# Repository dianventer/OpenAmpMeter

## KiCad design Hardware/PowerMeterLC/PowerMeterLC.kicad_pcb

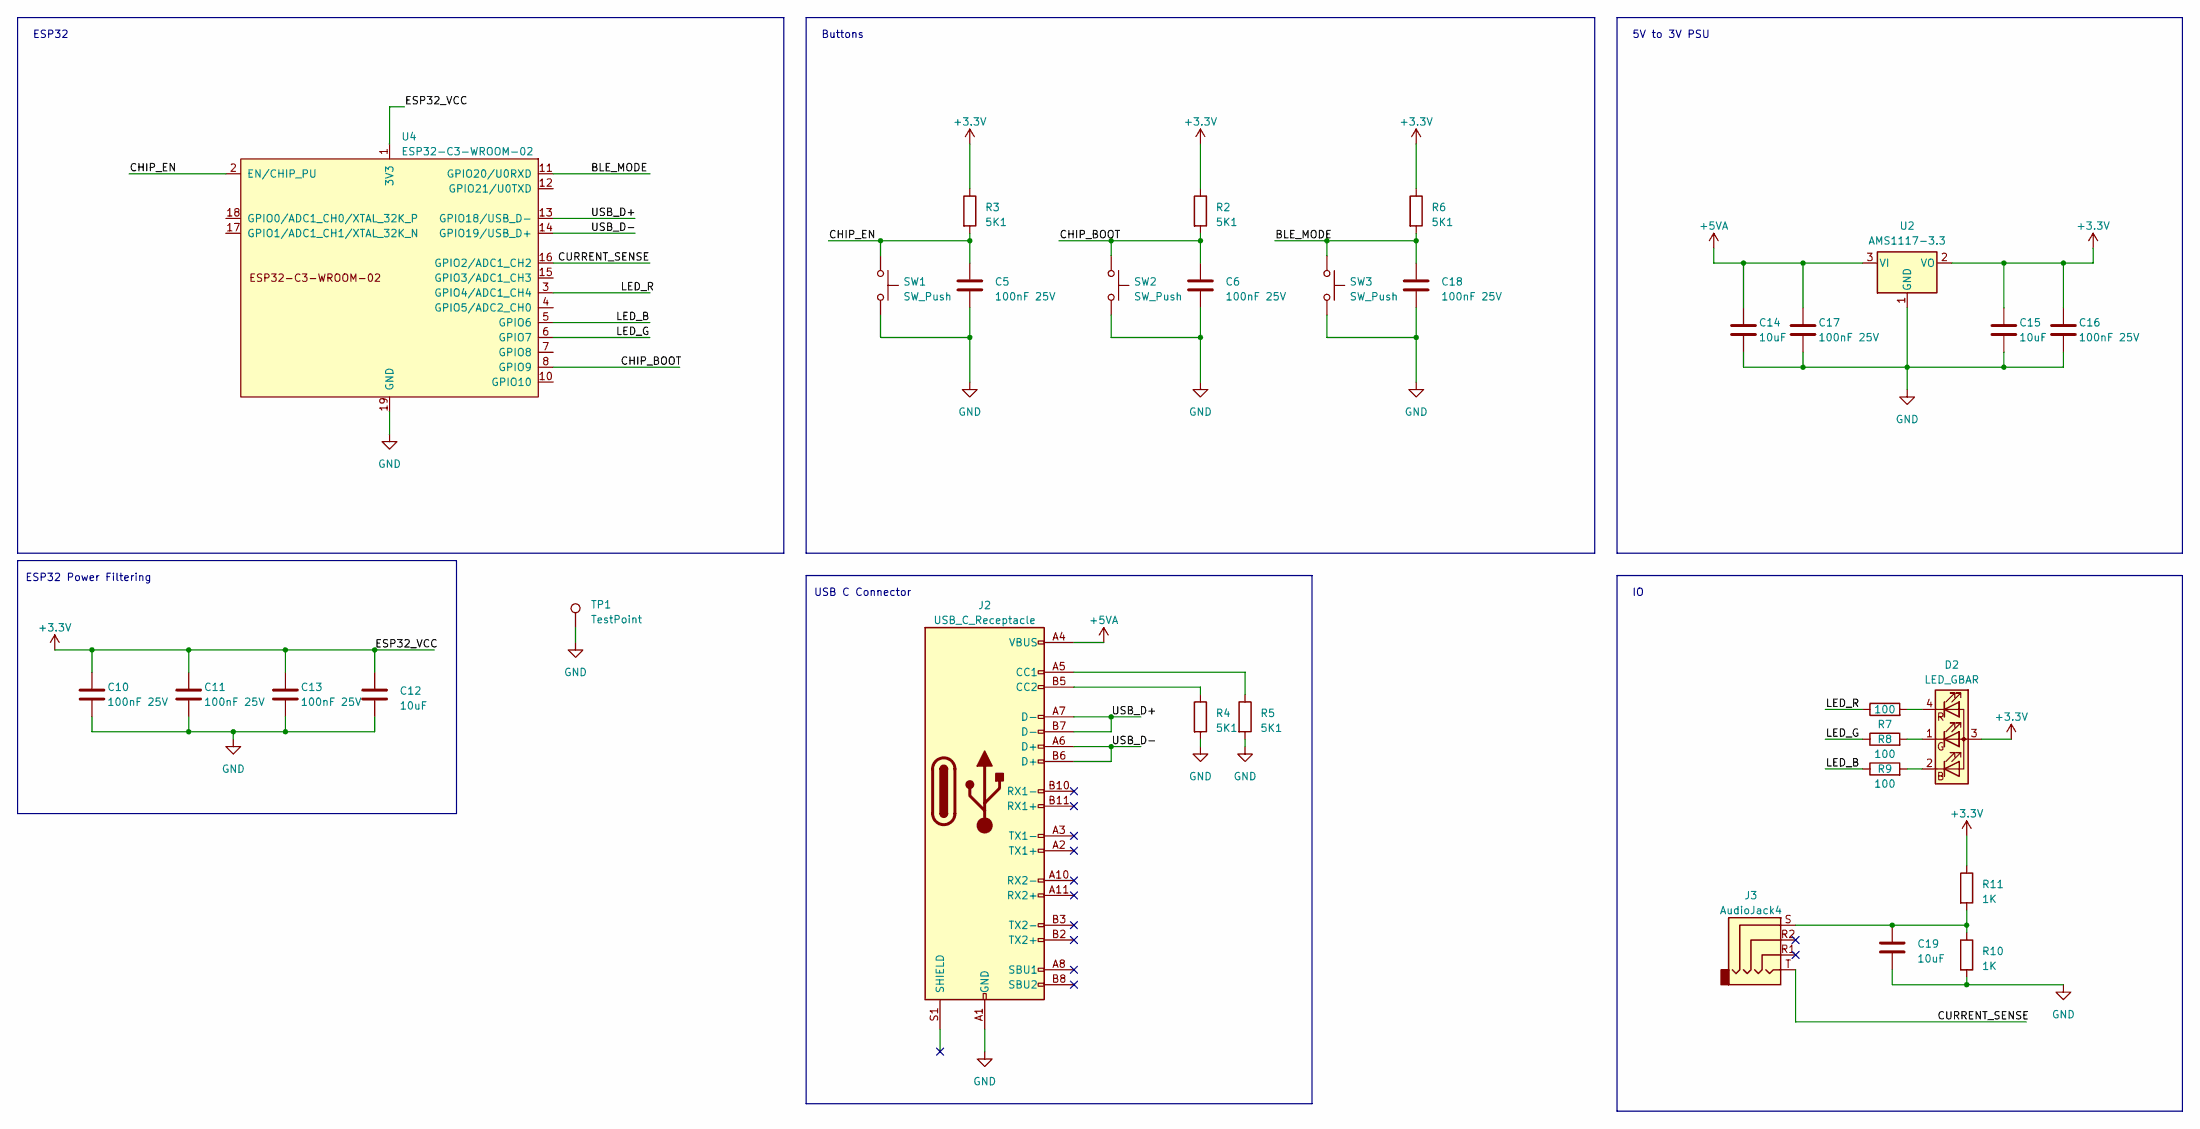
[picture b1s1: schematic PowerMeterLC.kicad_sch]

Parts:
C5, C6, C10, C11, C13, C16, C17, C18: 100nF 25V; C_0603_1608Metric; LCSC C2857981
C12, C14, C15, C19: 10uF; C_0805_2012Metric; LCSC C385035
D2: LED_GBAR; LED_D5.0mm-4_RGB; LCSC C2827302
J2: USB_C_Receptacle; USB_C_Receptacle_Palconn_UTC16-G; LCSC C2927038
J3: AudioJack4; Jack_3.5mm_PJ320E_Horizontal; LCSC C431535
R2, R3, R4, R5, R6: 5K1; R_0603_1608Metric; LCSC C269696
R7, R8, R9: 100; R_0603_1608Metric; LCSC C22775
R10, R11: 1K; R_0603_1608Metric; LCSC C21190
SW1, SW2, SW3: SW_Push; SW_SPST_CK_RS282G05A3; LCSC C495942
TP1: TestPoint; MountingHole_2.5mm_Pad_Via
U2: AMS1117-3.3; SOT-223-3_TabPin2; LCSC C347222
U4: ESP32-C3-WROOM-02

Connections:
+3V3: C10.1, C11.1, C12.1, C13.1, C15.1, C16.1, D2.3 (A), R2.1, R3.1, R6.1, R11.1, U2.2 (VO), U4.1 (3V3)
+5VA: C14.1, C17.1, J2.A4 (VBUS), J2.A9 (VBUS), J2.B4 (VBUS), J2.B9 (VBUS), U2.3 (VI)
/BLE_MODE: C18.1, R6.2, SW3.1, U4.11 (GPIO20/U0RXD)
/CHIP_BOOT: C6.1, R2.2, SW2.1, U4.8 (GPIO9)
/CHIP_EN: C5.1, R3.2, SW1.1, U4.2 (EN/CHIP_PU)
/CURRENT_SENSE: J3.T, U4.16 (GPIO2/ADC1_CH2)
/LED_B: R9.1, U4.5 (GPIO6)
/LED_G: R8.1, U4.6 (GPIO7)
/LED_R: R7.1, U4.3 (GPIO4/ADC1_CH4)
/USB_D+: J2.A7 (D-), J2.B7 (D-), U4.13 (GPIO18/USB_D-)
/USB_D-: J2.A6 (D+), J2.B6 (D+), U4.14 (GPIO19/USB_D+)
GND: C5.2, C6.2, C10.2, C11.2, C12.2, C13.2, C14.2, C15.2, C16.2, C17.2, C18.2, C19.2, J2.A1 (GND), J2.A12 (GND), J2.B1 (GND), J2.B12 (GND), R4.2, R5.2, R10.2, SW1.2, SW2.2, SW3.2, TP1.1, U2.1 (GND), U4.9 (GND), U4.19 (GND)
unnamed: C19.1, J3.S, R10.1, R11.2
unnamed: D2.2 (BK), R9.2
unnamed: D2.1 (GK), R8.2
unnamed: D2.4 (RK), R7.2
unnamed: J2.A5 (CC1), R5.1
unnamed: J2.B5 (CC2), R4.1

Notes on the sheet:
Buttons
5V to 3V PSU
USB C Connector
ESP32
ESP32 Power Filtering

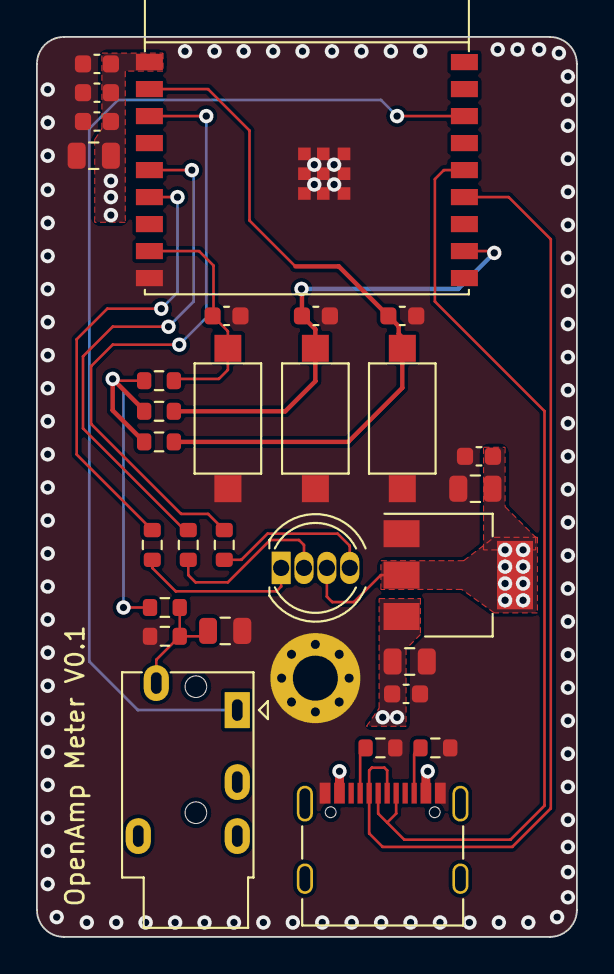
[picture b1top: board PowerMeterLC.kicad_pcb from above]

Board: 4 copper layers, 30.0 x 50.0 mm, 31 parts (0 on the bottom side), 18 nets.

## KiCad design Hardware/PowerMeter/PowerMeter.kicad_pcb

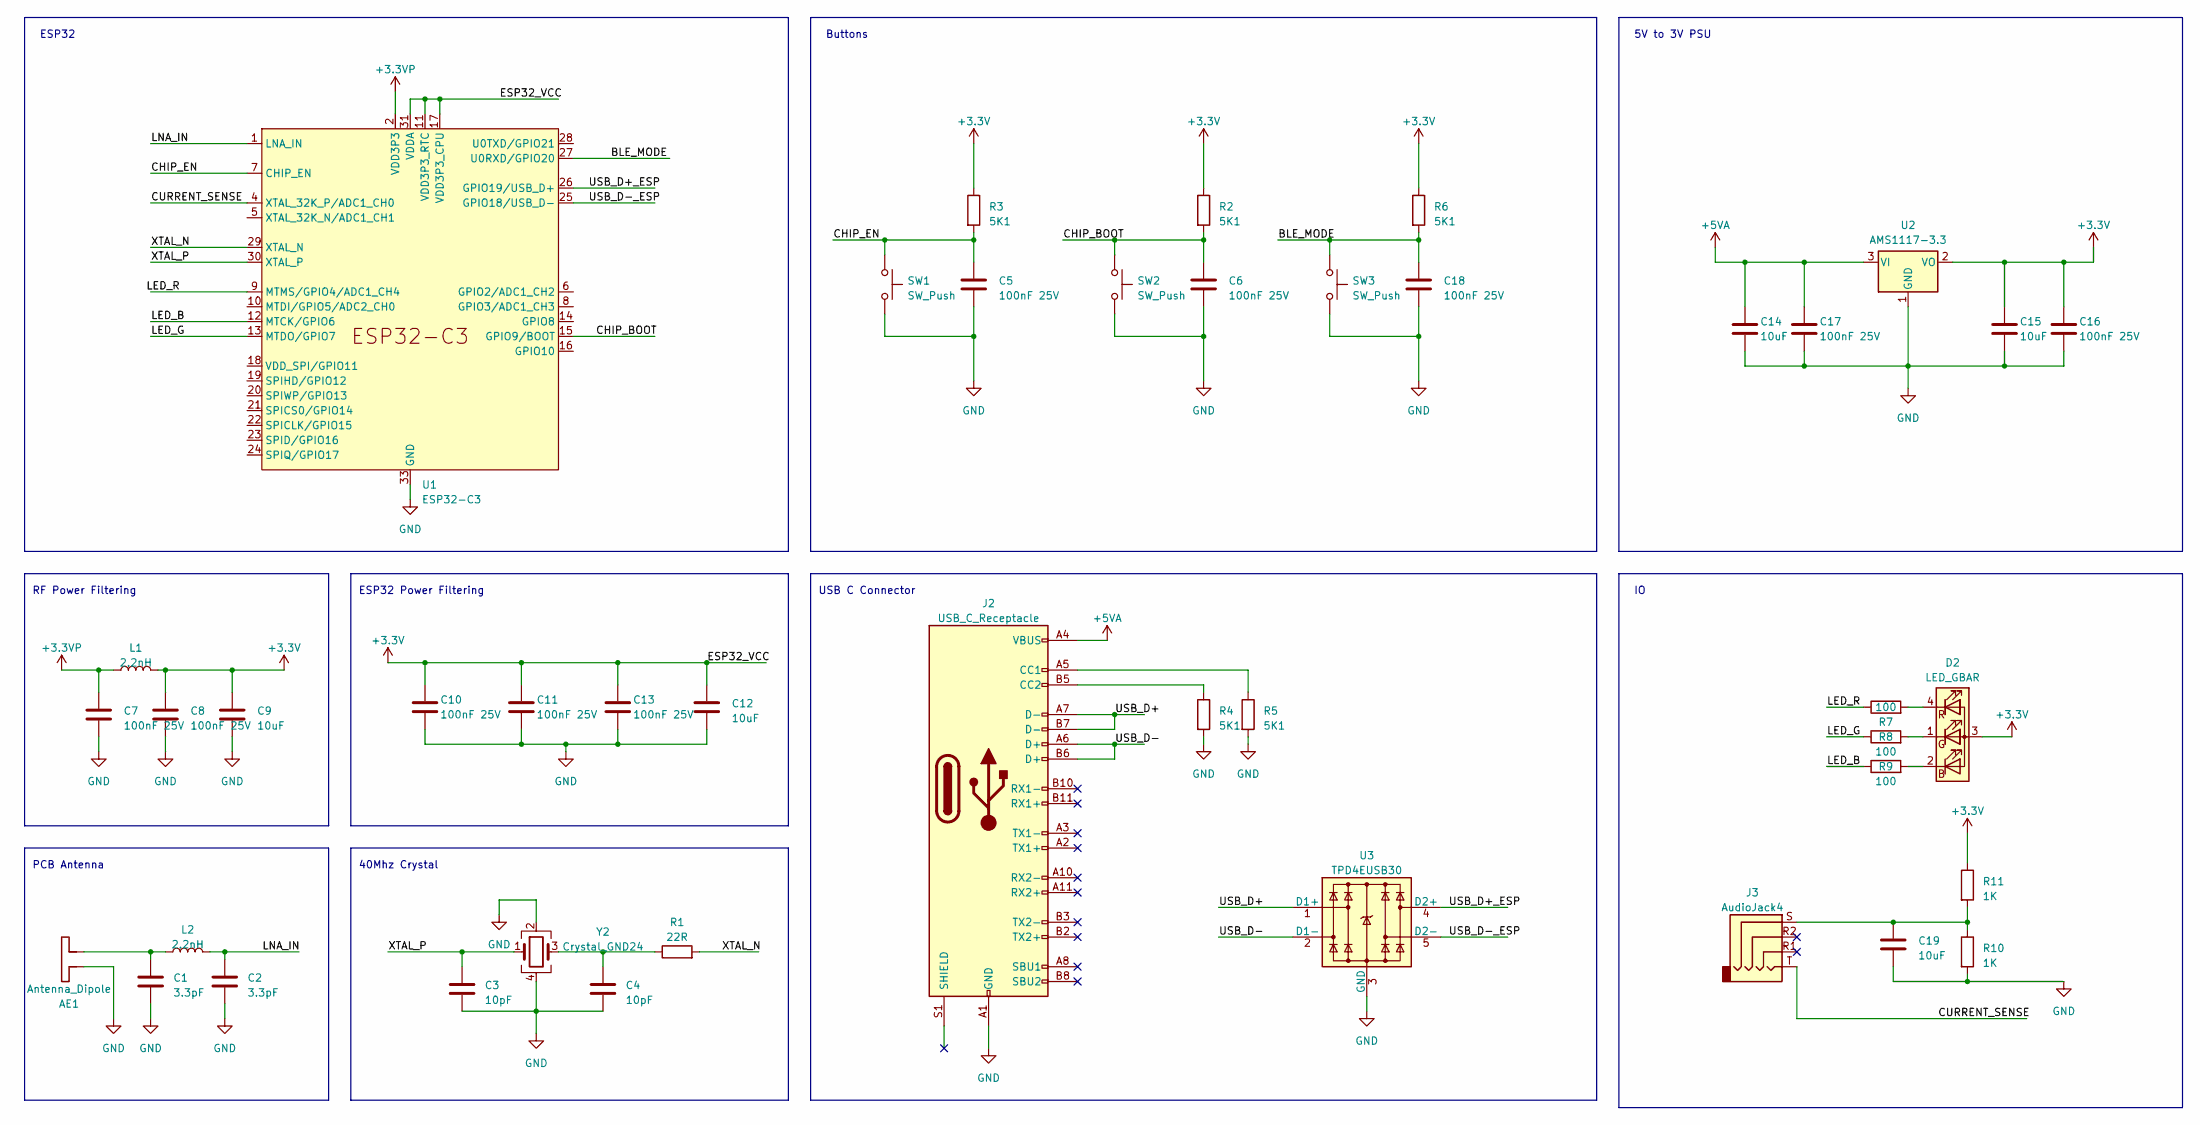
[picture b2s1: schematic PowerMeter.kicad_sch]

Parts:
AE1: Antenna_Dipole; Texas_SWRA117D_2.4GHz_Left
C1, C2: 3.3pF; C_0603_1608Metric; LCSC C5360819
C3, C4: 10pF; C_0402_1005Metric; LCSC C3152489
C5, C6, C7, C8, C10, C11, C13, C16, C17, C18: 100nF 25V; C_0603_1608Metric; LCSC C2857981
C9, C12, C14, C15, C19: 10uF; C_0603_1608Metric; LCSC C385035
D2: LED_GBAR; LED_RGB_1210; LCSC C2827302
J2: USB_C_Receptacle; USB_C_Receptacle_Palconn_UTC16-G; LCSC C2927038
J3: AudioJack4; Jack_3.5mm_PJ320D_Horizontal; LCSC C431535
L1, L2: 2.2nH; L_0603_1608Metric; LCSC C370334
R1: 22R; R_0402_1005Metric; LCSC C3015957
R2, R3, R4, R5, R6: 5K1; R_0603_1608Metric; LCSC C269696
R7, R8, R9: 100; R_0603_1608Metric; LCSC C22775
R10, R11: 1K; R_0603_1608Metric; LCSC C21190
SW1, SW2, SW3: SW_Push; SW_Push_SPST_NO_Alps_SKRK; LCSC C495942
U1: ESP32-C3; QFN-32-1EP_5x5mm_P0.5mm_EP3.45x3.45mm; LCSC C5143572
U2: AMS1117-3.3; SOT-223-3_TabPin2; LCSC C347222
U3: TPD4EUSB30; USON-10_2.5x1.0mm_P0.5mm; LCSC C90627
Y2: Crystal_GND24; Crystal_SMD_3225-4Pin_3.2x2.5mm; LCSC C2875284

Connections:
+3.3VP: C7.1, L1.1, U1.2 (VDD3P3), U1.3 (VDD3P3)
+3V3: C8.1, C9.1, C10.1, C11.1, C12.1, C13.1, C15.1, C16.1, D2.3 (A), L1.2, R2.1, R3.1, R6.1, R11.1, U1.11 (VDD3P3_RTC), U1.17 (VDD3P3_CPU), U1.31 (VDDA), U1.32 (VDDA), U2.2 (VO)
+5VA: C14.1, C17.1, J2.A4 (VBUS), J2.A9 (VBUS), J2.B4 (VBUS), J2.B9 (VBUS), U2.3 (VI)
/BLE_MODE: C18.1, R6.2, SW3.1, U1.27 (U0RXD/GPIO20)
/CHIP_BOOT: C6.1, R2.2, SW2.1, U1.15 (GPIO9/BOOT)
/CHIP_EN: C5.1, R3.2, SW1.1, U1.7 (CHIP_EN)
/CURRENT_SENSE: J3.T, U1.4 (XTAL_32K_P/ADC1_CH0)
/LED_B: R9.1, U1.12 (MTCK/GPIO6)
/LED_G: R8.1, U1.13 (MTDO/GPIO7)
/LED_R: R7.1, U1.9 (MTMS/GPIO4/ADC1_CH4)
/LNA_IN: C2.1, L2.2, U1.1 (LNA_IN)
/USB_D+: J2.A7 (D-), J2.B7 (D-), U3.1 (D1+)
/USB_D+_ESP: U1.26 (GPIO19/USB_D+), U3.4 (D2+)
/USB_D-: J2.A6 (D+), J2.B6 (D+), U3.2 (D1-)
/USB_D-_ESP: U1.25 (GPIO18/USB_D-), U3.5 (D2-)
/XTAL_N: R1.2, U1.29 (XTAL_N)
/XTAL_P: C3.1, U1.30 (XTAL_P), Y2.1
GND: AE1.2, C1.2, C2.2, C3.2, C4.2, C5.2, C6.2, C7.2, C8.2, C9.2, C10.2, C11.2, C12.2, C13.2, C14.2, C15.2, C16.2, C17.2, C18.2, C19.2, J2.A1 (GND), J2.A12 (GND), J2.B1 (GND), J2.B12 (GND), R4.2, R5.2, R10.2, SW1.2, SW2.2, SW3.2, U1.33 (GND), U2.1 (GND), U3.3 (GND), U3.8 (GND), Y2.2, Y2.4
unnamed: AE1.1, C1.1, L2.1
unnamed: C4.1, R1.1, Y2.3
unnamed: C19.1, J3.S, R10.1, R11.2
unnamed: D2.2 (BK), R9.2
unnamed: D2.1 (GK), R8.2
unnamed: D2.4 (RK), R7.2
unnamed: J2.A5 (CC1), R5.1
unnamed: J2.B5 (CC2), R4.1

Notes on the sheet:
Buttons
5V to 3V PSU
PCB Antenna
40Mhz Crystal
USB C Connector
RF Power Filtering
ESP32
ESP32 Power Filtering

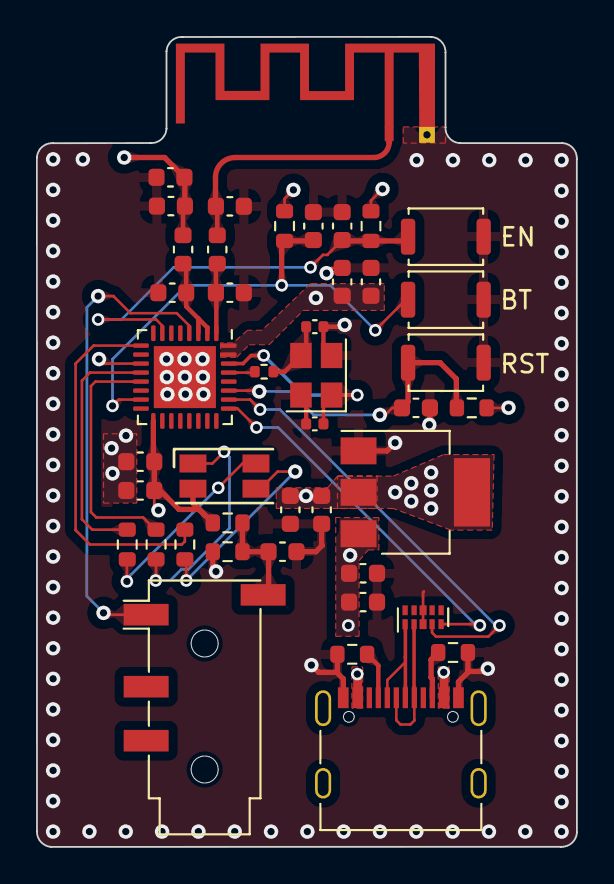
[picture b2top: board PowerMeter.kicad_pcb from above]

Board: 4 copper layers, 30.0 x 45.0 mm, 43 parts (0 on the bottom side), 26 nets.

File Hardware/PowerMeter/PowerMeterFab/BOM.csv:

Comment,Designator,Footprint,LCSC,Boards,Q,Quantity
3.3pF,"C1,C2",Capacitor_SMD:C_0603_1608Metric,C5360819,5,2,10
10pF,"C3,C4",Capacitor_SMD:C_0402_1005Metric,C3152489,5,2,10
100nF 25V,"C5,C6,C7,C8,C10,C11,C13,C16,C17,C18",Capacitor_SMD:C_0603_1608Metric,C2857981,5,10,50
10uF,"C9,C12,C14,C15,C19",Capacitor_SMD:C_0603_1608Metric,C385035,5,5,25
LED_GBAR,D2,LED_SMD:LED_RGB_1210,C2827302,5,1,5
USB_C_Receptacle,J2,Connector_USB:USB_C_Receptacle_Palconn_UTC16-G,C2927038,5,1,5
AudioJack4,J3,Connector_Audio:Jack_3.5mm_PJ320D_Horizontal,C431535,5,1,5
2.2nH,"L1,L2",Inductor_SMD:L_0603_1608Metric,C370334,5,2,10
22R,R1,Resistor_SMD:R_0402_1005Metric,C3015957,5,1,5
1K,"R10,R11",Resistor_SMD:R_0603_1608Metric,C21190,5,2,10
5K1,"R2,R3,R4,R5,R6",Resistor_SMD:R_0603_1608Metric,C269696,5,5,25
100,"R7,R8,R9",Resistor_SMD:R_0603_1608Metric,C22775,5,3,15
SW_Push,"SW1,SW2,SW3",Button_Switch_SMD:SW_Push_SPST_NO_Alps_SKRK,C495942,5,3,15
ESP32-C3,U1,Package_DFN_QFN:QFN-32-1EP_5x5mm_P0.5mm_EP3.45x3.45mm,C5143572,5,1,5
AMS1117-3.3,U2,Package_TO_SOT_SMD:SOT-223-3_TabPin2,C347222,5,1,5
TPD4EUSB30,U3,Package_SON:USON-10_2.5x1.0mm_P0.5mm,C90627,5,1,5
Crystal_GND24,Y2,Crystal:Crystal_SMD_3225-4Pin_3.2x2.5mm,C2875284,5,1,5

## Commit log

2023-05-28 OpenAmpMeter Initial Commit
2024-02-11 sjwo
